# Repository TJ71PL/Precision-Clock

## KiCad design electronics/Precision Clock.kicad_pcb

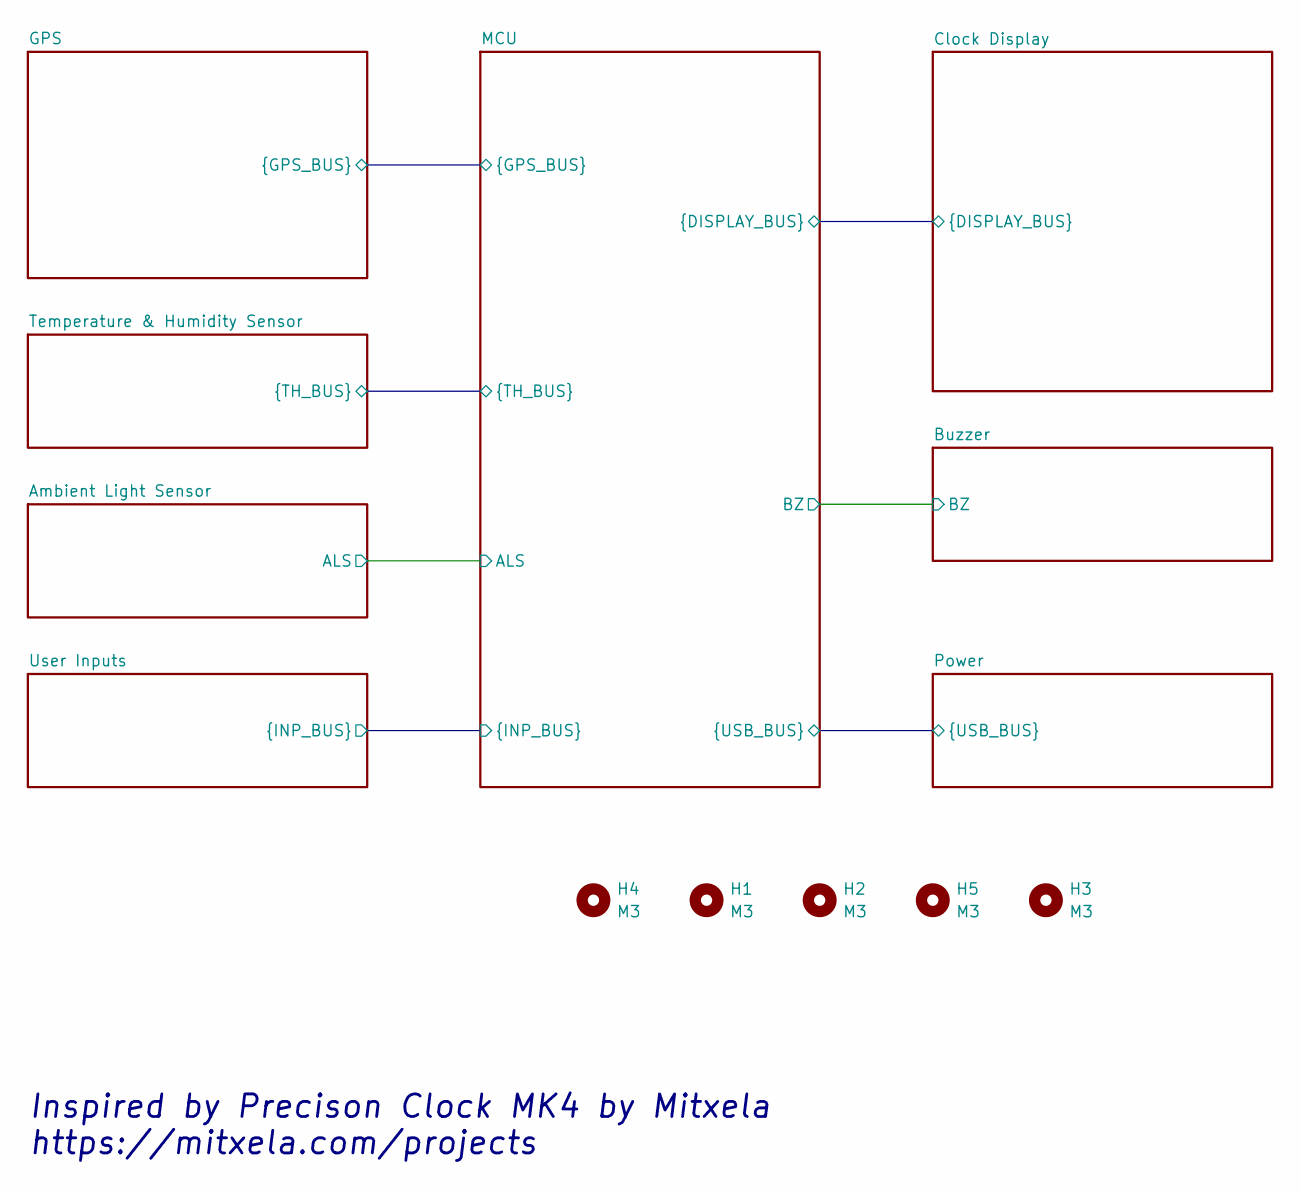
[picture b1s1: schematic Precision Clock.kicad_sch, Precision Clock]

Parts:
H1, H2, H3, H4, H5: M3; MountingHole_3.2mm_M3

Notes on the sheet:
Inspired by Precison Clock MK4 by Mitxela https://mitxela.com/projects

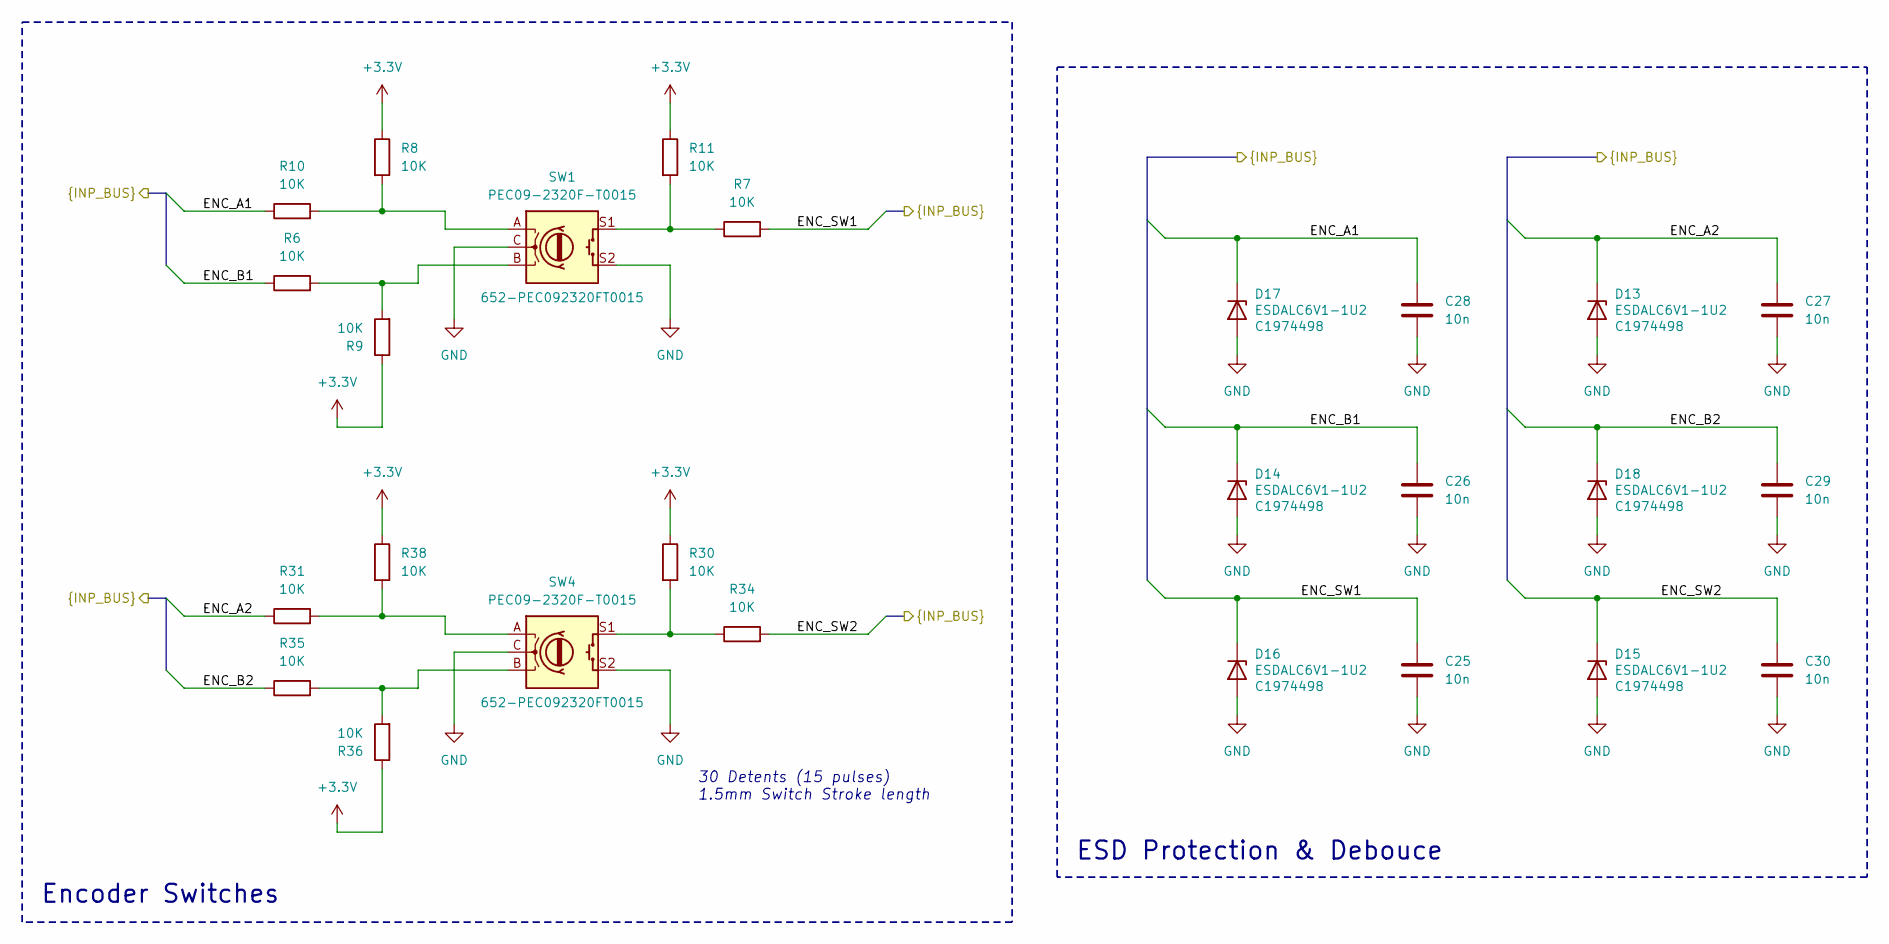
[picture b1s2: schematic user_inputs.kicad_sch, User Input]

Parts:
C25, C26, C27, C28, C29, C30: 10n; C_0402_1005Metric; LCSC C15195
D13, D14, D15, D16, D17, D18: ESDALC6V1-1U2; ST ESDALC6V1-1U2; LCSC C1974498
R6, R7, R8, R9, R10, R11, R30, R31, R34, R35, R36, R38: 10K; R_0402_1005Metric; LCSC C60489
SW1, SW4: PEC09-2320F-T0015; RotaryEncoder_Bourns_Horizontal_PEC09-2xxxF-Txxxx; Mouser 652-PEC092320FT0015

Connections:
+3.3V: R8.1, R9.1, R11.1, R30.1, R36.1, R38.1; also elsewhere on the board
/MCU/ENC_A1: C28.1, D17.1 (K), R10.1; also elsewhere on the board
/MCU/ENC_A2: C27.1, D13.1 (K), R31.1; also elsewhere on the board
/MCU/ENC_B1: C26.1, D14.1 (K), R6.1; also elsewhere on the board
/MCU/ENC_B2: C29.1, D18.1 (K), R35.1; also elsewhere on the board
/MCU/ENC_SW1: C25.1, D16.1 (K), R7.2; also elsewhere on the board
/MCU/ENC_SW2: C30.1, D15.1 (K), R34.2; also elsewhere on the board
GND: C25.2, C26.2, C27.2, C28.2, C29.2, C30.2, D13.2 (A), D14.2 (A), D15.2 (A), D16.2 (A), D17.2 (A), D18.2 (A), SW1.C, SW1.S2, SW4.C, SW4.S2; also elsewhere on the board
unnamed: R6.2, R9.2, SW1.B
unnamed: R8.2, R10.2, SW1.A
unnamed: R7.1, R11.2, SW1.S1
unnamed: R30.2, R34.1, SW4.S1
unnamed: R31.2, R38.2, SW4.A
unnamed: R35.2, R36.2, SW4.B

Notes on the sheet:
Encoder Switches
ESD Protection & Debouce
30 Detents (15 pulses) 1.5mm Switch Stroke length

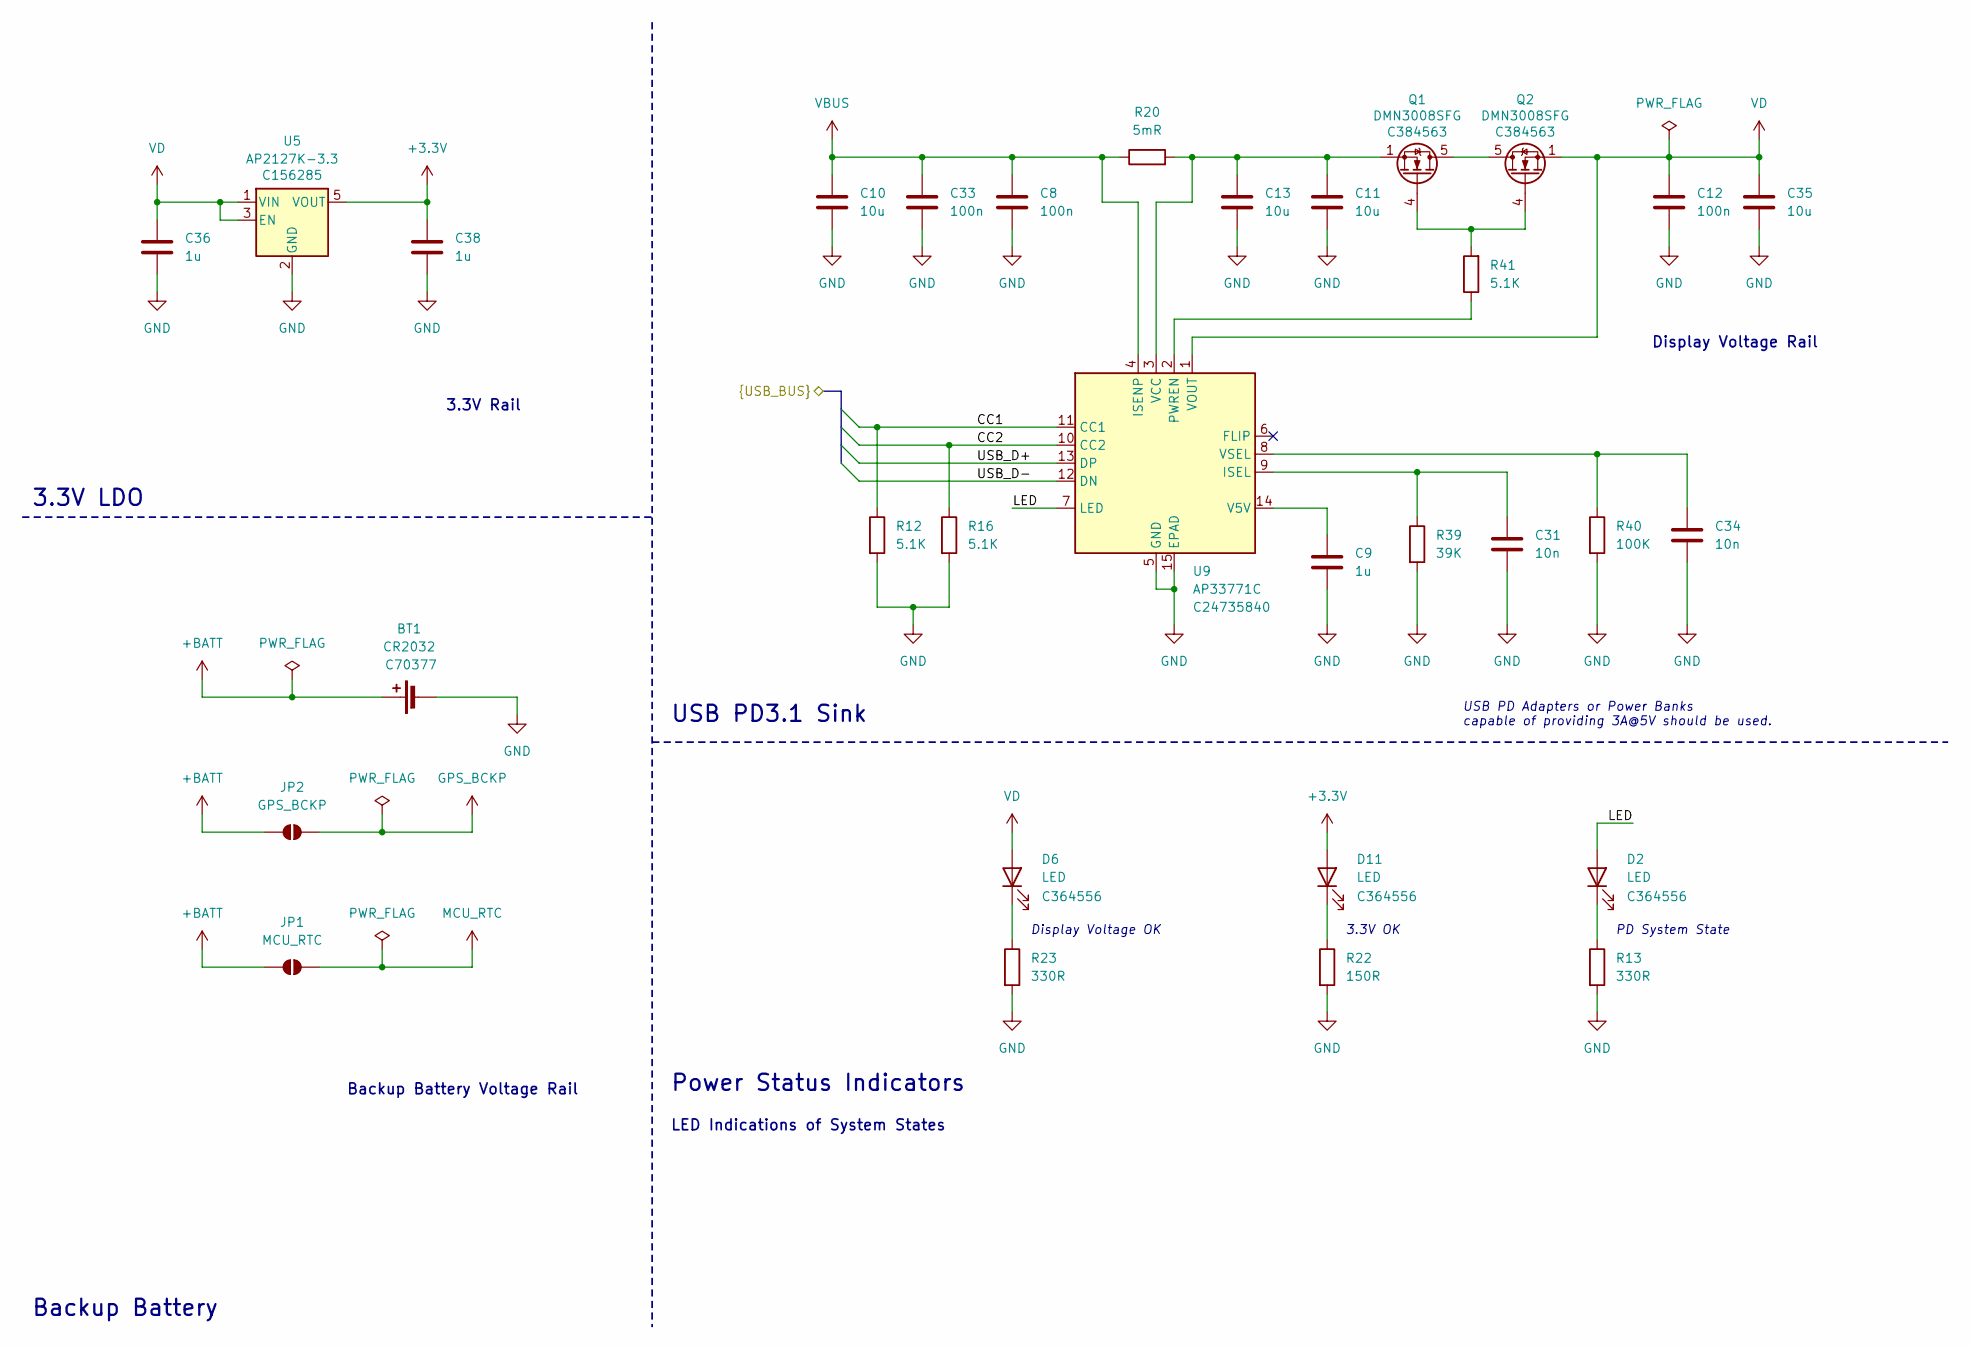
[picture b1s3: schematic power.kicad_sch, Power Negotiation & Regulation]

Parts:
BT1: CR2032; Battery_holder_CR2032_SMD; LCSC C70377
C8, C12, C33: 100n; C_0402_1005Metric; LCSC C1525
C9, C36, C38: 1u; C_0402_1005Metric; LCSC C29266
C10, C11, C13, C35: 10u; C_0603_1608Metric; LCSC C86275
C31, C34: 10n; C_0402_1005Metric; LCSC C15195
D2, D6, D11: LED; LED_LiteON_LTST-C281KGKT; LCSC C364556
JP1: MCU_RTC; SolderJumper-2_P1.3mm_Open_TrianglePad1.0x1.5mm
JP2: GPS_BCKP; SolderJumper-2_P1.3mm_Open_TrianglePad1.0x1.5mm
Q1, Q2: DMN3008SFG; Diodes_PowerDI3333-8; LCSC C384563
R12, R16, R41: 5.1K; R_0402_1005Metric; LCSC C105872
R13, R23: 330R; R_0402_1005Metric; LCSC C276273
R20: 5mR; R_0805_2012Metric; LCSC C92742
R22: 150R; R_0402_1005Metric; LCSC C276273
R39: 39K; R_0402_1005Metric; LCSC C137995
R40: 100K; R_0402_1005Metric; LCSC C60491
U5: AP2127K-3.3; SOT-23-5; LCSC C156285
U9: AP33771C; W-DFN3030-14 (Type A1) Diodes; LCSC C24735840

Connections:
+3.3V: C38.1, D11.2 (A), U5.5 (VOUT); also elsewhere on the board
+BATT: BT1.1 (+), JP1.1 (A), JP2.1 (A)
/MCU/CC1: R12.1, U9.11 (CC1); also elsewhere on the board
/MCU/CC2: R16.1, U9.10 (CC2); also elsewhere on the board
/MCU/USB_D+: U9.13 (DP); also elsewhere on the board
/MCU/USB_D-: U9.12 (DN); also elsewhere on the board
/Power/LED: D2.2 (A), U9.7 (LED)
GND: BT1.2 (-), C8.2, C9.2, C10.2, C11.2, C12.2, C13.2, C31.2, C33.2, C34.2, C35.2, C36.2, C38.2, R12.2, R13.2, R16.2, R22.2, R23.2, R39.2, R40.2, U5.2 (GND), U9.5 (GND), U9.15 (EPAD); also elsewhere on the board
GPS_BCKP: JP2.2 (B); also elsewhere on the board
MCU_RTC: JP1.2 (B); also elsewhere on the board
unnamed: D2.1 (K), R13.1
unnamed: D6.1 (K), R23.1
unnamed: D11.1 (K), R22.1
unnamed: Q1.5 (D), Q2.5 (D)
unnamed: Q1.4 (G), Q2.4 (G), R41.2
unnamed: C31.1, R39.1, U9.9 (ISEL)
unnamed: R41.1, U9.2 (PWREN)
unnamed: C9.1, U9.14 (V5V)
unnamed: C11.1, C13.1, Q1.1 (S), Q1.2 (S), Q1.3 (S), R20.2, U9.3 (VCC)
unnamed: C34.1, R40.1, U9.8 (VSEL)
VBUS: C8.1, C10.1, C33.1, R20.1, U9.4 (ISENP); also elsewhere on the board
VD: C12.1, C35.1, C36.1, D6.2 (A), Q2.1 (S), Q2.2 (S), Q2.3 (S), U5.1 (VIN), U5.3 (EN), U9.1 (VOUT); also elsewhere on the board

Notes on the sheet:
LED Indications of System States
Backup Battery
3.3V LDO
USB PD Adapters or Power Banks capable of providing 3A@5V should be used.
3.3V OK
PD System State
Display Voltage OK
Display Voltage Rail
3.3V Rail
Backup Battery Voltage Rail
Power Status Indicators
USB PD3.1 Sink

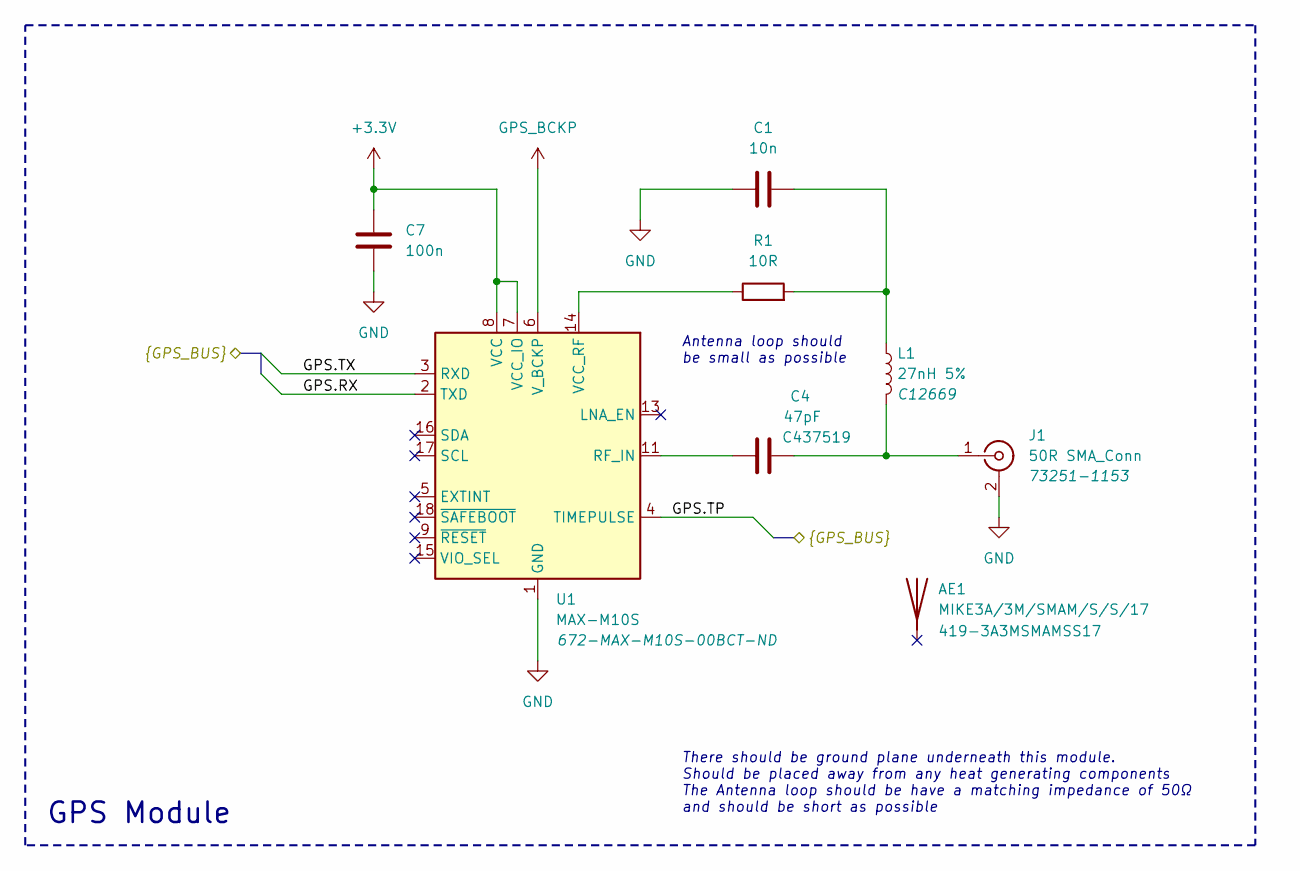
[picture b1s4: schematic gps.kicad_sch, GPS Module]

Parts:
AE1: MIKE3A/3M/SMAM/S/S/17; Mouser 419-3A3MSMAMSS17
C1: 10n; C_0402_1005Metric; LCSC C15195
C4: 47pF; C_0402_1005Metric; LCSC C437519
C7: 100n; C_0402_1005Metric; LCSC C1525
J1: 50R SMA_Conn; SMA_Molex_73251-1153_EdgeMount_Horizontal; Mouser 73251-1153
L1: 27nH 5%; L_0402_1005Metric; LCSC C12669
R1: 10R; R_0603_1608Metric; LCSC C109318
U1: MAX-M10S; ublox_MAX; Digikey 672-MAX-M10S-00BCT-ND

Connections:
+3.3V: C7.1, U1.7 (VCC_IO), U1.8 (VCC); also elsewhere on the board
/GPS/GPS.RX: U1.2 (TXD); also elsewhere on the board
/GPS/GPS.TP: U1.4 (TIMEPULSE); also elsewhere on the board
/GPS/GPS.TX: U1.3 (RXD); also elsewhere on the board
GND: C1.1, C7.2, J1.2 (Ext), U1.1 (GND), U1.10 (GND), U1.12 (GND); also elsewhere on the board
GPS_BCKP: U1.6 (V_BCKP); also elsewhere on the board
unnamed: C1.2, L1.1, R1.2
unnamed: C4.2, J1.1 (In), L1.2
unnamed: C4.1, U1.11 (RF_IN)
unnamed: R1.1, U1.14 (VCC_RF)

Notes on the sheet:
Antenna loop should be small as possible
GPS Module
There should be ground plane underneath this module. Should be placed away from any heat generating components The Antenna loop should be have a matching impedance of 50Ω and should be short as possible

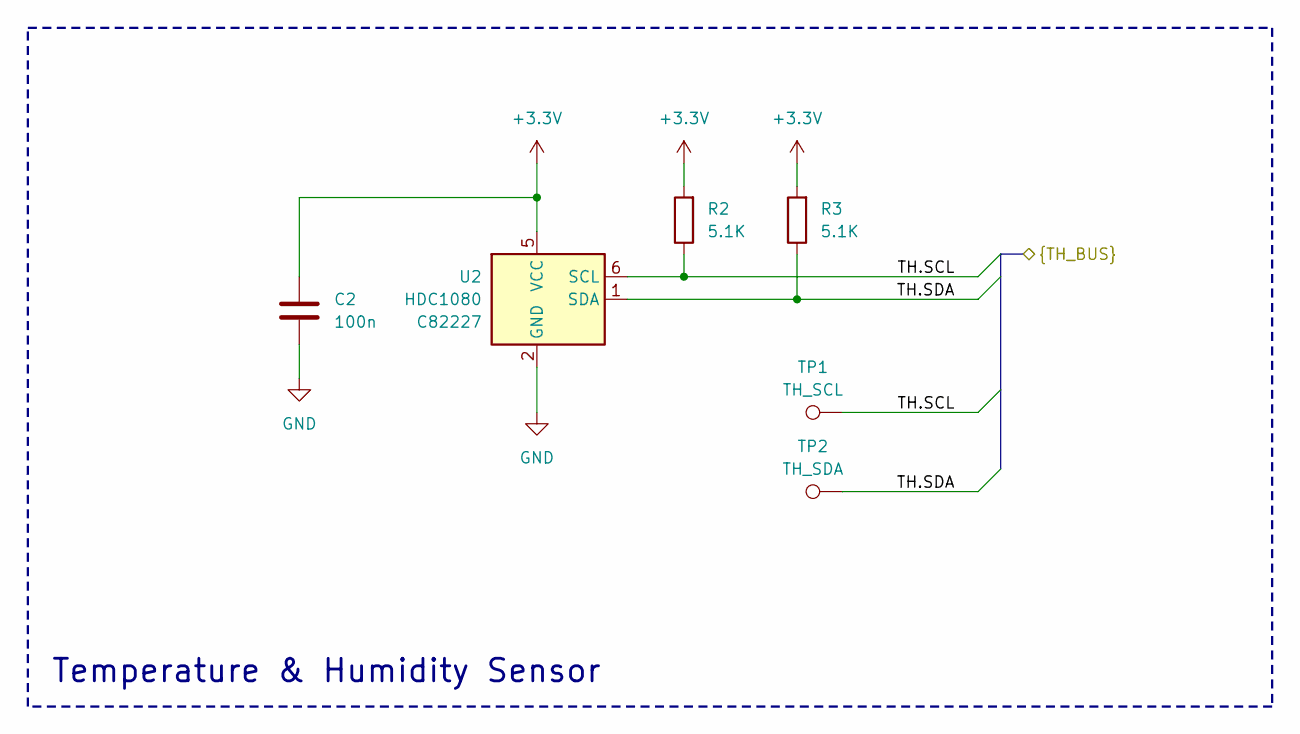
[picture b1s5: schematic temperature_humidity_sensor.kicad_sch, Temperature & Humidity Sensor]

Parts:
C2: 100n; C_0402_1005Metric; LCSC C1525
R2, R3: 5.1K; R_0402_1005Metric; LCSC C105872
TP1: TH_SCL; TestPoint_Pad_D1.0mm
TP2: TH_SDA; TestPoint_Pad_D1.0mm
U2: HDC1080; Texas_PWSON-N6; LCSC C82227

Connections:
+3.3V: C2.1, R2.2, R3.2, U2.5 (VCC); also elsewhere on the board
/MCU/TH.SCL: R2.1, TP1.1, U2.6 (SCL); also elsewhere on the board
/MCU/TH.SDA: R3.1, TP2.1, U2.1 (SDA); also elsewhere on the board
GND: C2.2, U2.2 (GND); also elsewhere on the board

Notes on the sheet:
Temperature & Humidity Sensor

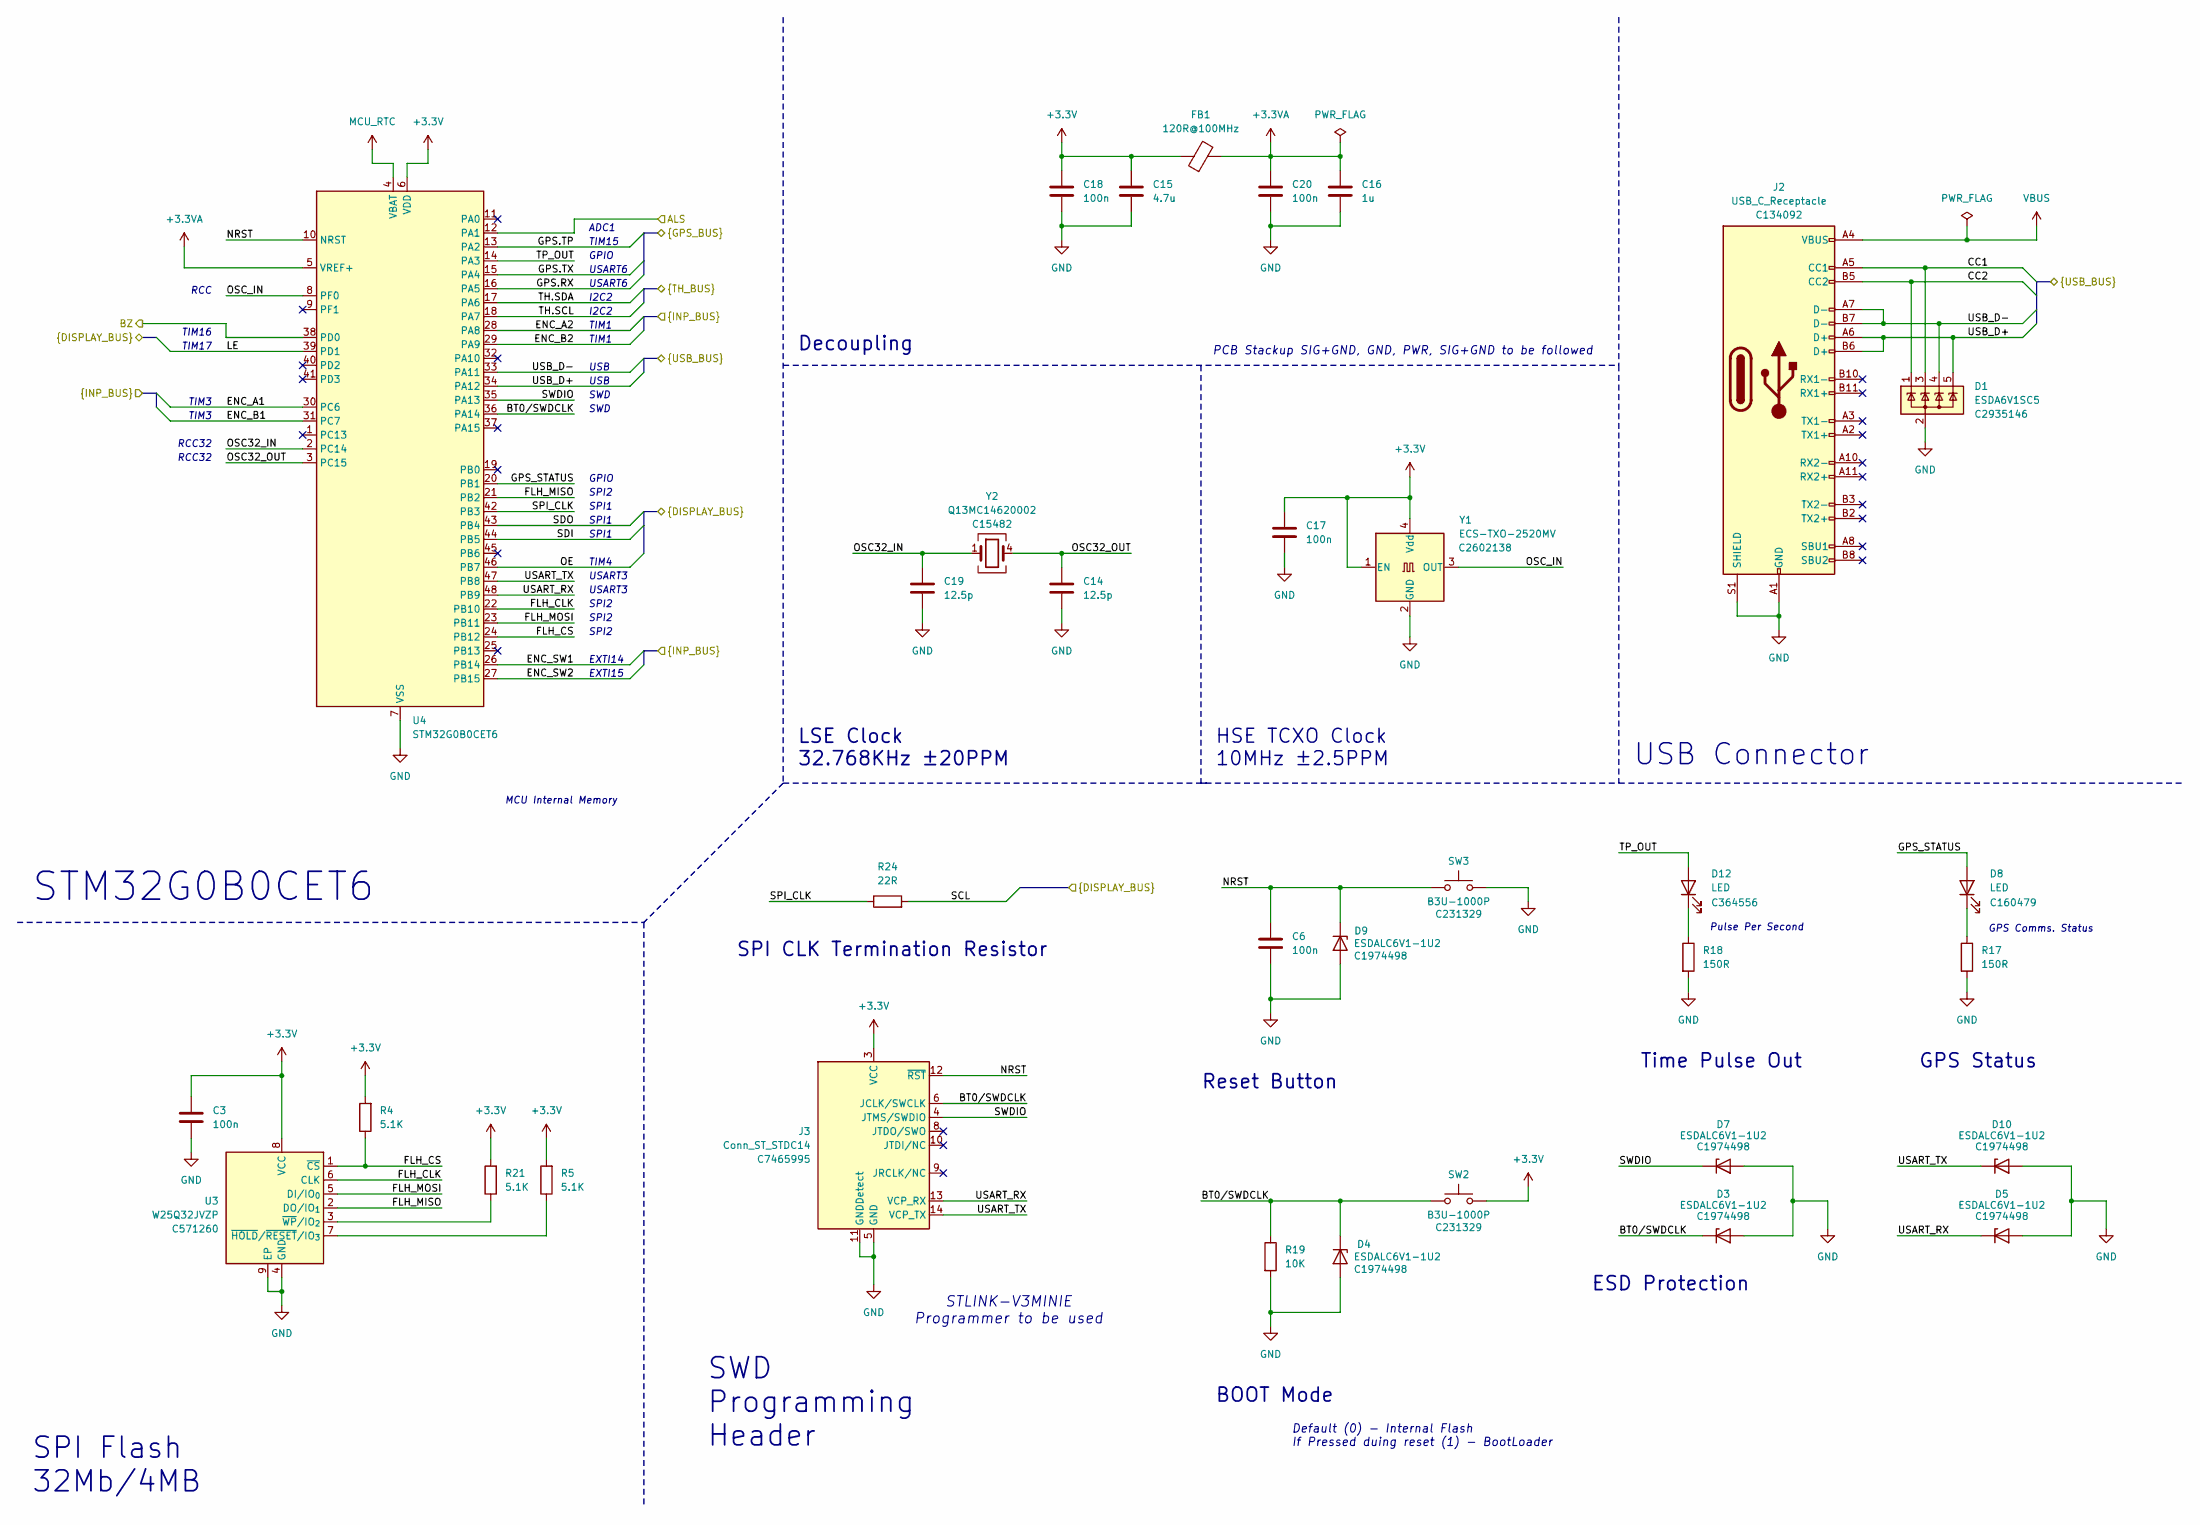
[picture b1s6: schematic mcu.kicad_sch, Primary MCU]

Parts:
C3, C6, C17, C18, C20: 100n; C_0402_1005Metric; LCSC C1525
C14, C19: 12.5p; C_0402_1005Metric; LCSC C26406
C15: 4.7u; C_0603_1608Metric; LCSC C69335
C16: 1u; C_0402_1005Metric; LCSC C29266
D1: ESDA6V1SC5; SOT-23-5; LCSC C2935146
D3, D4, D5, D7, D9, D10: ESDALC6V1-1U2; ST ESDALC6V1-1U2; LCSC C1974498
D8: LED; LED_LiteON_LTST-C281KGKT; LCSC C160479
D12: LED; LED_LiteON_LTST-C281KGKT; LCSC C364556
FB1: 120R@100MHz; R_0402_1005Metric; LCSC C38480
J2: USB_C_Receptacle; USB_C_Receptacle_Molex_105450-0101; LCSC C134092
J3: Conn_ST_STDC14; ST STDC14; LCSC C7465995
R4, R5, R21: 5.1K; R_0402_1005Metric; LCSC C105872
R17, R18: 150R; R_0402_1005Metric; LCSC C137936
R19: 10K; R_0402_1005Metric; LCSC C60489
R24: 22R; R_0402_1005Metric; LCSC C109318
SW2, SW3: B3U-1000P; SW_SPST_B3U-1000P; LCSC C231329
U3: W25Q32JVZP; WSON-8-1EP_6x5mm_P1.27mm_EP3.4x4.3mm; LCSC C571260
U4: STM32G0B0CET6; LQFP-48_7x7mm_P0.5mm; LCSC C2826978
Y1: ECS-TXO-2520MV; ECS_TXO-2520MV; LCSC C2602138
Y2: Q13MC14620002; Crystal_SMD_SeikoEpson_MC146-4Pin_6.7x1.5mm; LCSC C15482

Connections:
+3.3V: C3.1, C15.1, C17.1, C18.1, FB1.1, J3.3 (VCC), R4.2, R5.2, R21.2, SW2.2, U3.8 (VCC), U4.6 (VDD), Y1.1 (EN), Y1.4 (Vdd); also elsewhere on the board
+3.3VA: C16.1, C20.1, FB1.2, U4.5 (VREF+)
/Ambient Light Sensor/ALS: U4.12 (PA1); also elsewhere on the board
/Buzzer/BZ: U4.38 (PD0); also elsewhere on the board
/Clock Display/LE: U4.39 (PD1); also elsewhere on the board
/Clock Display/OE: U4.46 (PB7); also elsewhere on the board
/Clock Display/SCL: R24.2; also elsewhere on the board
/Clock Display/SDI: U4.44 (PB5); also elsewhere on the board
/Clock Display/SDO: U4.43 (PB4); also elsewhere on the board
/GPS/GPS.RX: U4.16 (PA5); also elsewhere on the board
/GPS/GPS.TP: U4.13 (PA2); also elsewhere on the board
/GPS/GPS.TX: U4.15 (PA4); also elsewhere on the board
/MCU/BT0/SWDCLK: D3.1 (K), D4.1 (K), J3.6 (JCLK/SWCLK), R19.1, SW2.1, U4.36 (PA14)
/MCU/CC1: D1.3 (K), J2.A5 (CC1); also elsewhere on the board
/MCU/CC2: D1.1 (K), J2.B5 (CC2); also elsewhere on the board
/MCU/ENC_A1: U4.30 (PC6); also elsewhere on the board
/MCU/ENC_A2: U4.28 (PA8); also elsewhere on the board
/MCU/ENC_B1: U4.31 (PC7); also elsewhere on the board
/MCU/ENC_B2: U4.29 (PA9); also elsewhere on the board
/MCU/ENC_SW1: U4.26 (PB14); also elsewhere on the board
/MCU/ENC_SW2: U4.27 (PB15); also elsewhere on the board
/MCU/FLH_CLK: U3.6 (CLK), U4.22 (PB10)
/MCU/FLH_CS: R4.1, U3.1 (~CS), U4.24 (PB12)
/MCU/FLH_MISO: U3.2 (DO/IO_{1}), U4.21 (PB2)
/MCU/FLH_MOSI: U3.5 (DI/IO_{0}), U4.23 (PB11)
/MCU/GPS_STATUS: D8.2 (A), U4.20 (PB1)
/MCU/NRST: C6.2, D9.1 (K), J3.12 (~RST), SW3.1, U4.10 (NRST)
/MCU/OSC32_IN: C19.1, U4.2 (PC14), Y2.1
/MCU/OSC32_OUT: C14.1, U4.3 (PC15), Y2.4 (3)
/MCU/OSC_IN: U4.8 (PF0), Y1.3 (OUT)
/MCU/SPI_CLK: R24.1, U4.42 (PB3)
/MCU/SWDIO: D7.1 (K), J3.4 (JTMS/SWDIO), U4.35 (PA13)
/MCU/TH.SCL: U4.18 (PA7); also elsewhere on the board
/MCU/TH.SDA: U4.17 (PA6); also elsewhere on the board
/MCU/TP_OUT: D12.2 (A), U4.14 (PA3)
/MCU/USART_RX: D5.1 (K), J3.13 (VCP_RX), U4.48 (PB9)
/MCU/USART_TX: D10.1 (K), J3.14 (VCP_TX), U4.47 (PB8)
/MCU/USB_D+: D1.5 (K), J2.A6 (D+), J2.B6 (D+), U4.34 (PA12); also elsewhere on the board
/MCU/USB_D-: D1.4 (K), J2.A7 (D-), J2.B7 (D-), U4.33 (PA11); also elsewhere on the board
GND: C3.2, C6.1, C14.2, C15.2, C16.2, C17.2, C18.2, C19.2, C20.2, D1.2 (A), D3.2 (A), D4.2 (A), D5.2 (A), D7.2 (A), D9.2 (A), D10.2 (A), J2.A1 (GND), J2.A12 (GND), J2.B1 (GND), J2.B12 (GND), J2.S1 (SHIELD), J3.5 (GND), J3.7 (GND), J3.11 (GNDDetect), R17.2, R18.2, R19.2, SW3.2, U3.4 (GND), U3.9 (EP), U4.7 (VSS), Y1.2 (GND); also elsewhere on the board
MCU_RTC: U4.4 (VBAT); also elsewhere on the board
unnamed: D8.1 (K), R17.1
unnamed: D12.1 (K), R18.1
unnamed: R5.1, U3.7 (~HOLD/~RESET/IO_{3})
unnamed: R21.1, U3.3 (~WP/IO_{2})
VBUS: J2.A4 (VBUS), J2.A9 (VBUS), J2.B4 (VBUS), J2.B9 (VBUS); also elsewhere on the board

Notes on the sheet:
USB
SPI1
TIM4
SPI Flash 32Mb/4MB
LSE Clock 32.768KHz ±20PPM
TIM17
SPI2
Decoupling
PCB Stackup SIG+GND, GND, PWR, SIG+GND to be followed
GPS Comms. Status
USART6
TIM16
GPS Status
TIM1
GPIO
RCC32
I2C2
ESD Protection
EXTI14
Default (0) - Internal Flash If Pressed duing reset (1) - BootLoader
SWD Programming Header
Time Pulse Out
SWD
MCU Internal Memory
USART3
TIM3
Reset Button
HSE TCXO Clock 10MHz ±2.5PPM
STLINK-V3MINIE Programmer to be used
EXTI15
ADC1
BOOT Mode
SPI CLK Termination Resistor
RCC
TIM15
Pulse Per Second
USB Connector
STM32G0B0CET6

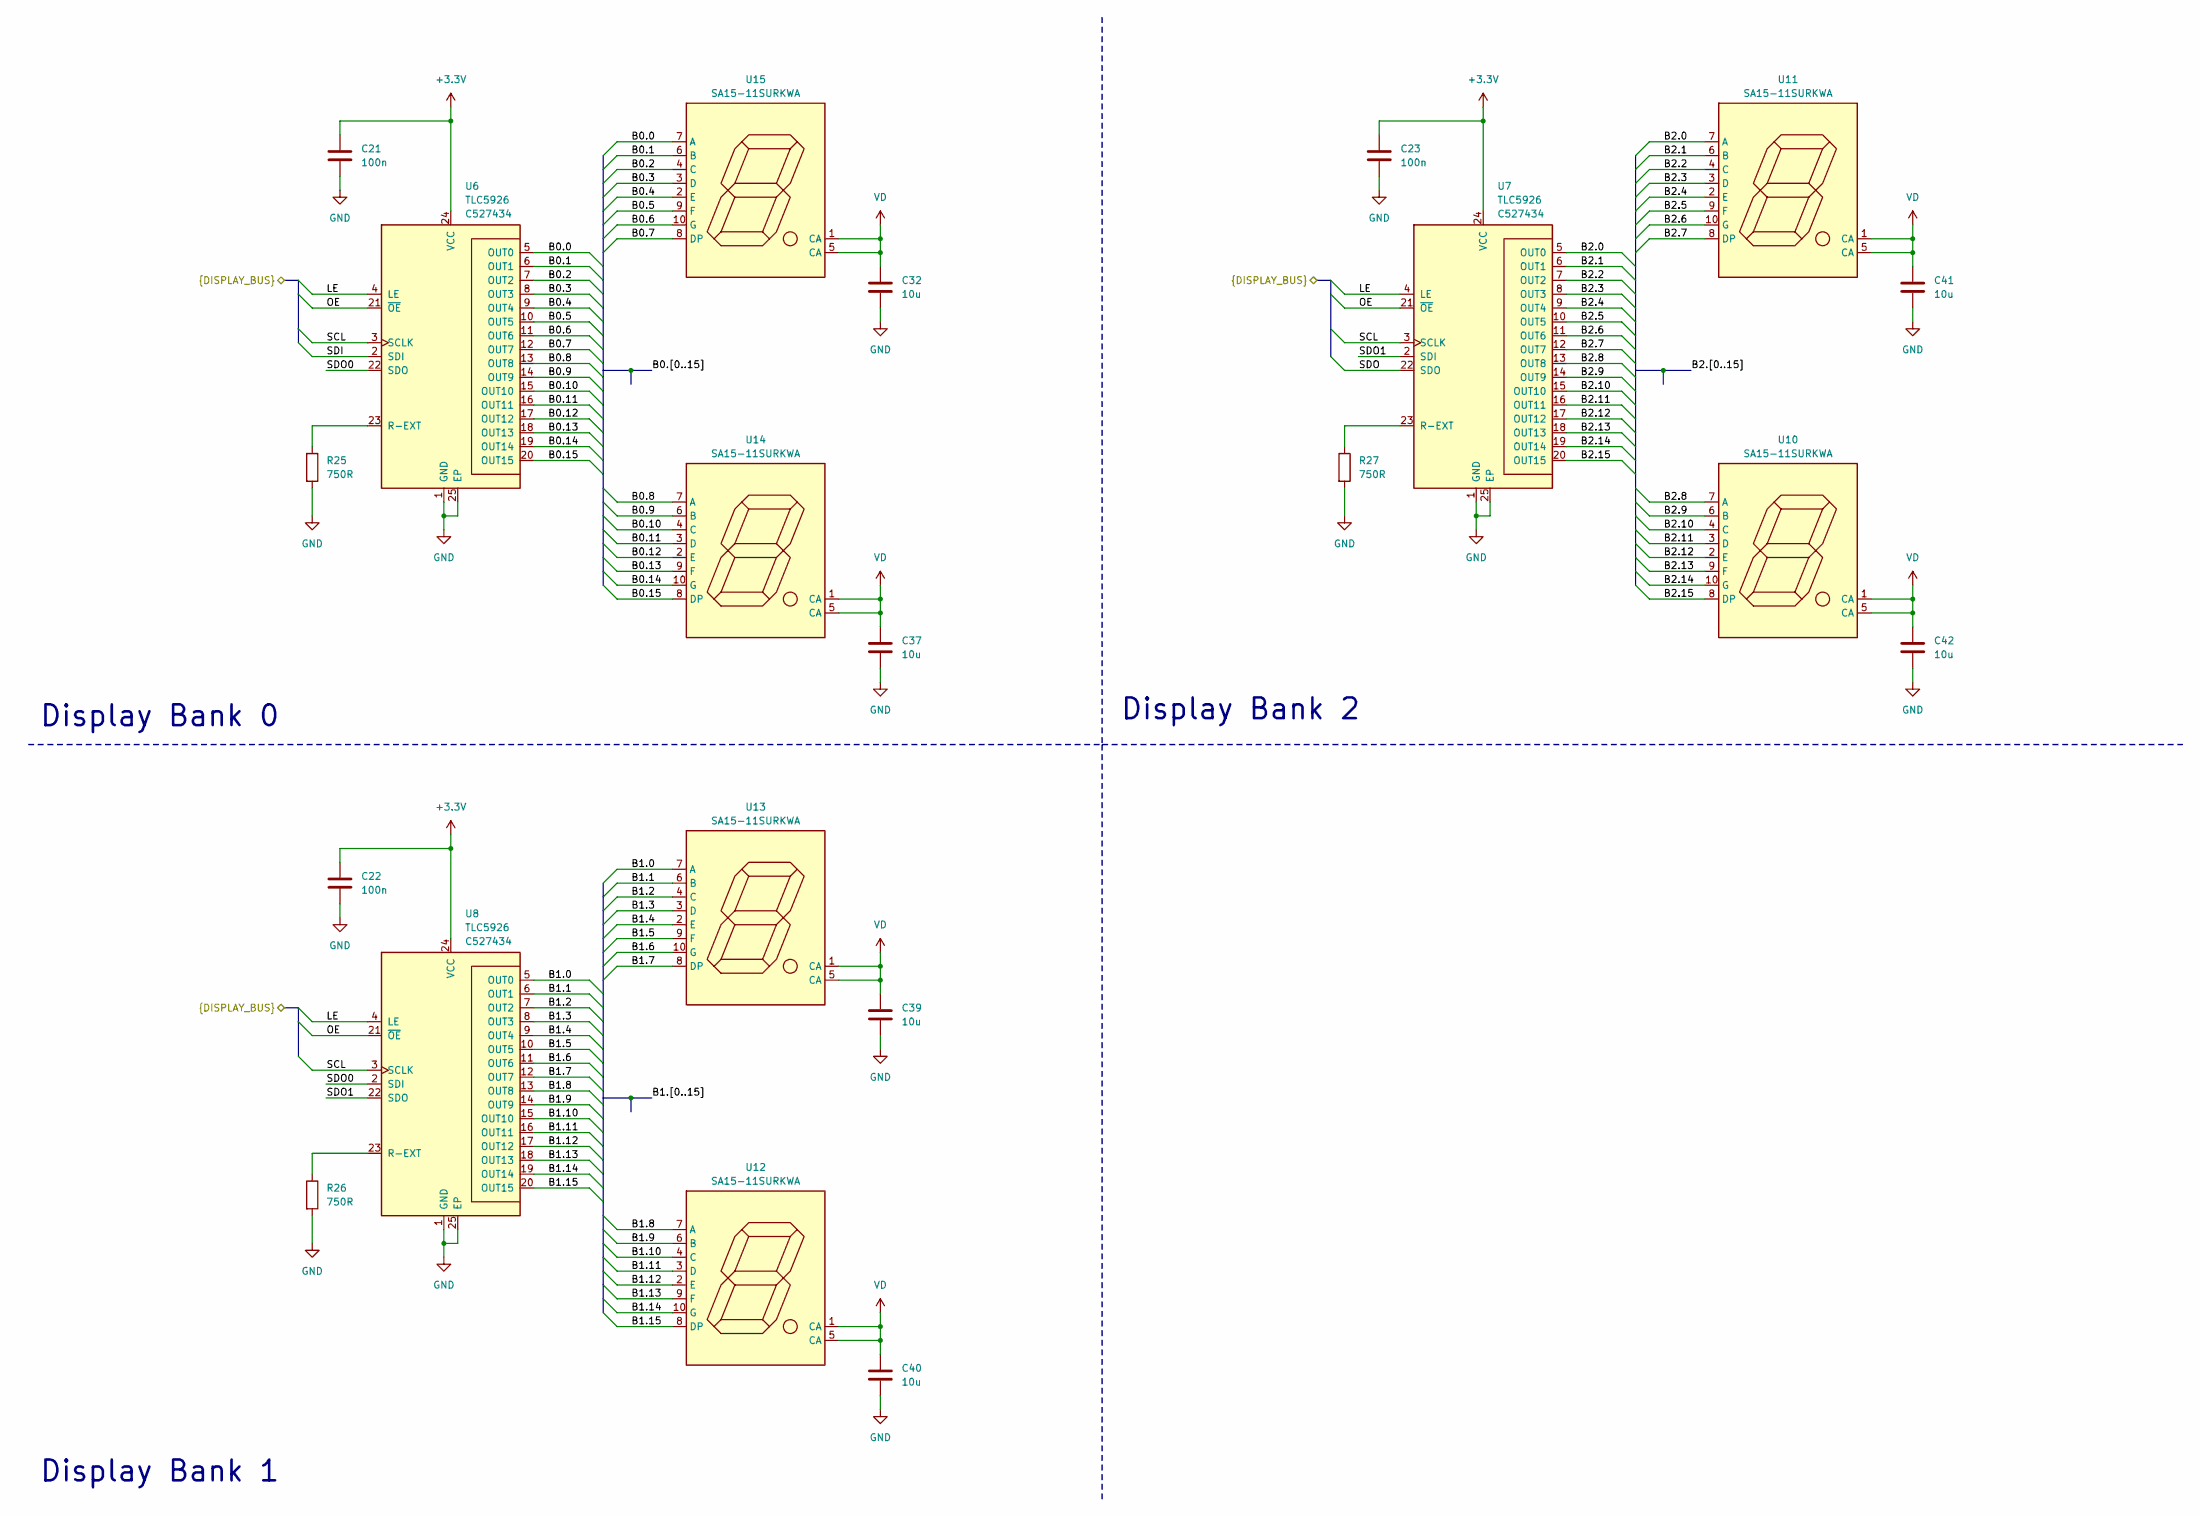
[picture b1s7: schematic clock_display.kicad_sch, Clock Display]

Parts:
C21, C22, C23: 100n; C_0402_1005Metric; LCSC C1525
C32, C37, C39, C40, C41, C42: 10u; C_0603_1608Metric; LCSC C86275
R25, R26, R27: 750R; R_0402_1005Metric; LCSC C137936
U6, U7, U8: TLC5926; HTSSOP-24-1EP_4.4x7.8mm_P0.65mm_EP3.2x5mm; LCSC C527434
U10, U11, U12, U13, U14, U15: SA15-11SURKWA

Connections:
+3.3V: C21.1, C22.1, C23.1, U6.24 (VCC), U7.24 (VCC), U8.24 (VCC); also elsewhere on the board
/Clock Display/B0.0: U6.5 (OUT0), U15.7 (A)
/Clock Display/B0.1: U6.6 (OUT1), U15.6 (B)
/Clock Display/B0.2: U6.7 (OUT2), U15.4 (C)
/Clock Display/B0.3: U6.8 (OUT3), U15.3 (D)
/Clock Display/B0.4: U6.9 (OUT4), U15.2 (E)
/Clock Display/B0.5: U6.10 (OUT5), U15.9 (F)
/Clock Display/B0.6: U6.11 (OUT6), U15.10 (G)
/Clock Display/B0.7: U6.12 (OUT7), U15.8 (DP)
/Clock Display/B0.8: U6.13 (OUT8), U14.7 (A)
/Clock Display/B0.9: U6.14 (OUT9), U14.6 (B)
/Clock Display/B0.10: U6.15 (OUT10), U14.4 (C)
/Clock Display/B0.11: U6.16 (OUT11), U14.3 (D)
/Clock Display/B0.12: U6.17 (OUT12), U14.2 (E)
/Clock Display/B0.13: U6.18 (OUT13), U14.9 (F)
/Clock Display/B0.14: U6.19 (OUT14), U14.10 (G)
/Clock Display/B0.15: U6.20 (OUT15), U14.8 (DP)
/Clock Display/B1.0: U8.5 (OUT0), U13.7 (A)
/Clock Display/B1.1: U8.6 (OUT1), U13.6 (B)
/Clock Display/B1.2: U8.7 (OUT2), U13.4 (C)
/Clock Display/B1.3: U8.8 (OUT3), U13.3 (D)
/Clock Display/B1.4: U8.9 (OUT4), U13.2 (E)
/Clock Display/B1.5: U8.10 (OUT5), U13.9 (F)
/Clock Display/B1.6: U8.11 (OUT6), U13.10 (G)
/Clock Display/B1.7: U8.12 (OUT7), U13.8 (DP)
/Clock Display/B1.8: U8.13 (OUT8), U12.7 (A)
/Clock Display/B1.9: U8.14 (OUT9), U12.6 (B)
/Clock Display/B1.10: U8.15 (OUT10), U12.4 (C)
/Clock Display/B1.11: U8.16 (OUT11), U12.3 (D)
/Clock Display/B1.12: U8.17 (OUT12), U12.2 (E)
/Clock Display/B1.13: U8.18 (OUT13), U12.9 (F)
/Clock Display/B1.14: U8.19 (OUT14), U12.10 (G)
/Clock Display/B1.15: U8.20 (OUT15), U12.8 (DP)
/Clock Display/B2.0: U7.5 (OUT0), U11.7 (A)
/Clock Display/B2.1: U7.6 (OUT1), U11.6 (B)
/Clock Display/B2.2: U7.7 (OUT2), U11.4 (C)
/Clock Display/B2.3: U7.8 (OUT3), U11.3 (D)
/Clock Display/B2.4: U7.9 (OUT4), U11.2 (E)
/Clock Display/B2.5: U7.10 (OUT5), U11.9 (F)
/Clock Display/B2.6: U7.11 (OUT6), U11.10 (G)
/Clock Display/B2.7: U7.12 (OUT7), U11.8 (DP)
/Clock Display/B2.8: U7.13 (OUT8), U10.7 (A)
/Clock Display/B2.9: U7.14 (OUT9), U10.6 (B)
/Clock Display/B2.10: U7.15 (OUT10), U10.4 (C)
/Clock Display/B2.11: U7.16 (OUT11), U10.3 (D)
/Clock Display/B2.12: U7.17 (OUT12), U10.2 (E)
/Clock Display/B2.13: U7.18 (OUT13), U10.9 (F)
/Clock Display/B2.14: U7.19 (OUT14), U10.10 (G)
/Clock Display/B2.15: U7.20 (OUT15), U10.8 (DP)
/Clock Display/LE: U6.4 (LE), U7.4 (LE), U8.4 (LE); also elsewhere on the board
/Clock Display/OE: U6.21 (~OE), U7.21 (~OE), U8.21 (~OE); also elsewhere on the board
/Clock Display/SCL: U6.3 (SCLK), U7.3 (SCLK), U8.3 (SCLK); also elsewhere on the board
/Clock Display/SDI: U6.2 (SDI); also elsewhere on the board
/Clock Display/SDO: U7.22 (SDO); also elsewhere on the board
/Clock Display/SDO0: U6.22 (SDO), U8.2 (SDI)
/Clock Display/SDO1: U7.2 (SDI), U8.22 (SDO)
GND: C21.2, C22.2, C23.2, C32.2, C37.2, C39.2, C40.2, C41.2, C42.2, R25.2, R26.2, R27.2, U6.1 (GND), U6.25 (EP), U7.1 (GND), U7.25 (EP), U8.1 (GND), U8.25 (EP); also elsewhere on the board
unnamed: R25.1, U6.23 (R-EXT)
unnamed: R27.1, U7.23 (R-EXT)
unnamed: R26.1, U8.23 (R-EXT)
VD: C32.1, C37.1, C39.1, C40.1, C41.1, C42.1, U10.1 (CA), U10.5 (CA), U11.1 (CA), U11.5 (CA), U12.1 (CA), U12.5 (CA), U13.1 (CA), U13.5 (CA), U14.1 (CA), U14.5 (CA), U15.1 (CA), U15.5 (CA); also elsewhere on the board

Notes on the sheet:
Display Bank 1
Display Bank 2
Display Bank 0
